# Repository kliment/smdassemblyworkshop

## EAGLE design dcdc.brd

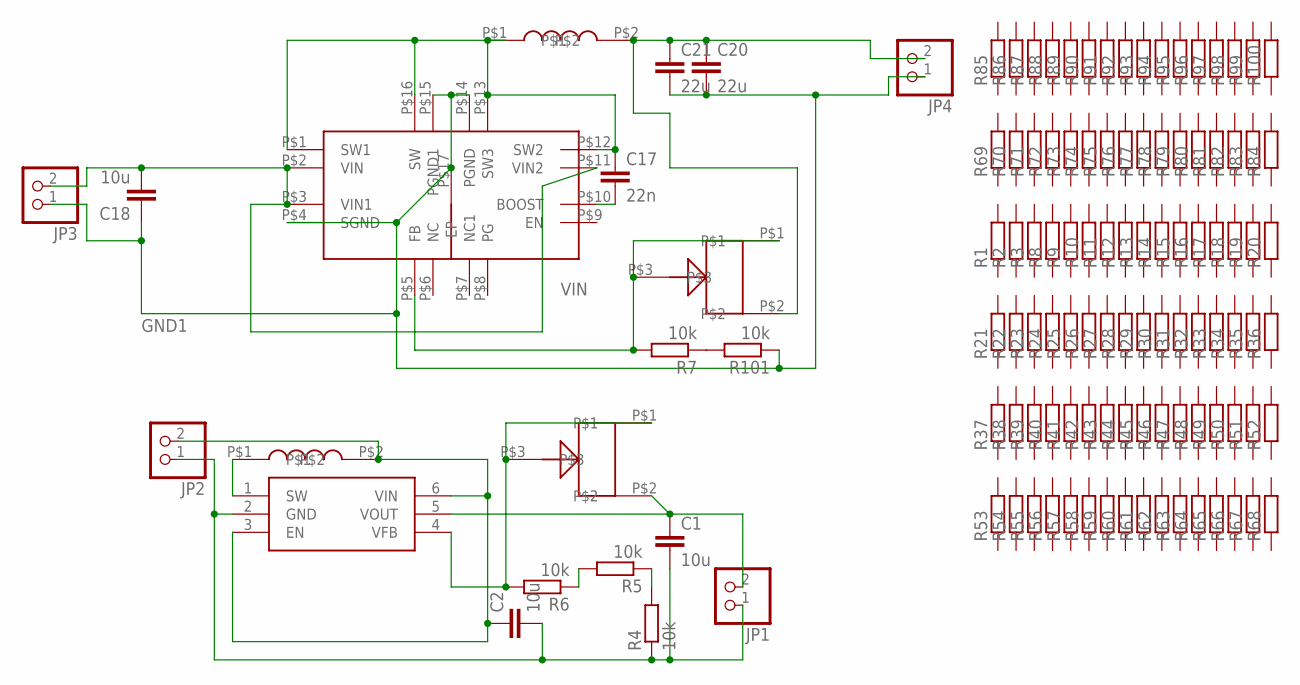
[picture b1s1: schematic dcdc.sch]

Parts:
C1, C2, C18: 10u; C1206K
C17: 22n; C0603
C20, C21: 22u; C1206K
JP1, JP2, JP3, JP4: PINHD-1X2; 1X02
R1, R2, R3, R8, R9, R10, R11, R12, R13, R14, R15, R16, R17, R18, R19, R20, R21, R22, R23, R24, R25, R26, R27, R28, R29, R30, R31, R32, R33, R34, R35, R36, R69, R70, R71, R72, R73, R74, R75, R76, R77, R78, R79, R80, R81, R82, R83, R84, R85, R86, R87, R88, R89, R90, R91, R92, R93, R94, R95, R96, R97, R98, R99, R100: R-EU_R0402; R0402
R4, R5, R6, R7, R101: 10k; R0603
R37, R38, R39, R40, R41, R42, R43, R44, R45, R46, R47, R48, R49, R50, R51, R52, R53, R54, R55, R56, R57, R58, R59, R60, R61, R62, R63, R64, R65, R66, R67, R68: R-EU_R0603; R0603
U$1, U$4: TRIMMER3MM
U$2: MCP1640SOT23-6; SOT23-6L
U$3: EPL2014
U$18: NR6028; NRS6
U$19: MCP16323; QFN16

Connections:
GND: C1.2, C2.2, JP1.1, JP2.1, R4.1, U$2.2 (GND)
GND1: C18.1, C20.2, C21.2, JP3.1, JP4.1, R101.1, U$19.P$4 (SGND), U$19.P$14 (PGND), U$19.P$15 (PGND1), U$19.P$17 (EP)
unnamed: R7.2, U$4.P$1, U$4.P$3, U$19.P$5 (FB)
unnamed: R4.2, R5.1
unnamed: C1.1, JP1.2, U$1.P$2, U$2.5 (VOUT)
unnamed: U$2.1 (SW), U$3.P$1
unnamed: R5.2, R6.1
unnamed: C2.1, JP2.2, U$2.3 (EN), U$2.6 (VIN), U$3.P$2
unnamed: R7.1, R101.2
unnamed: R6.2, U$1.P$1, U$1.P$3, U$2.4 (VFB)
unnamed: C17.2, U$19.P$10 (BOOST)
SW: C17.1, U$18.P$1, U$19.P$1 (SW1), U$19.P$12 (SW2), U$19.P$13 (SW3), U$19.P$16 (SW)
VIN: C18.2, JP3.2, U$19.P$2 (VIN), U$19.P$3 (VIN1), U$19.P$11 (VIN2)
VOUT: C20.1, C21.1, JP4.2, U$4.P$2, U$18.P$2

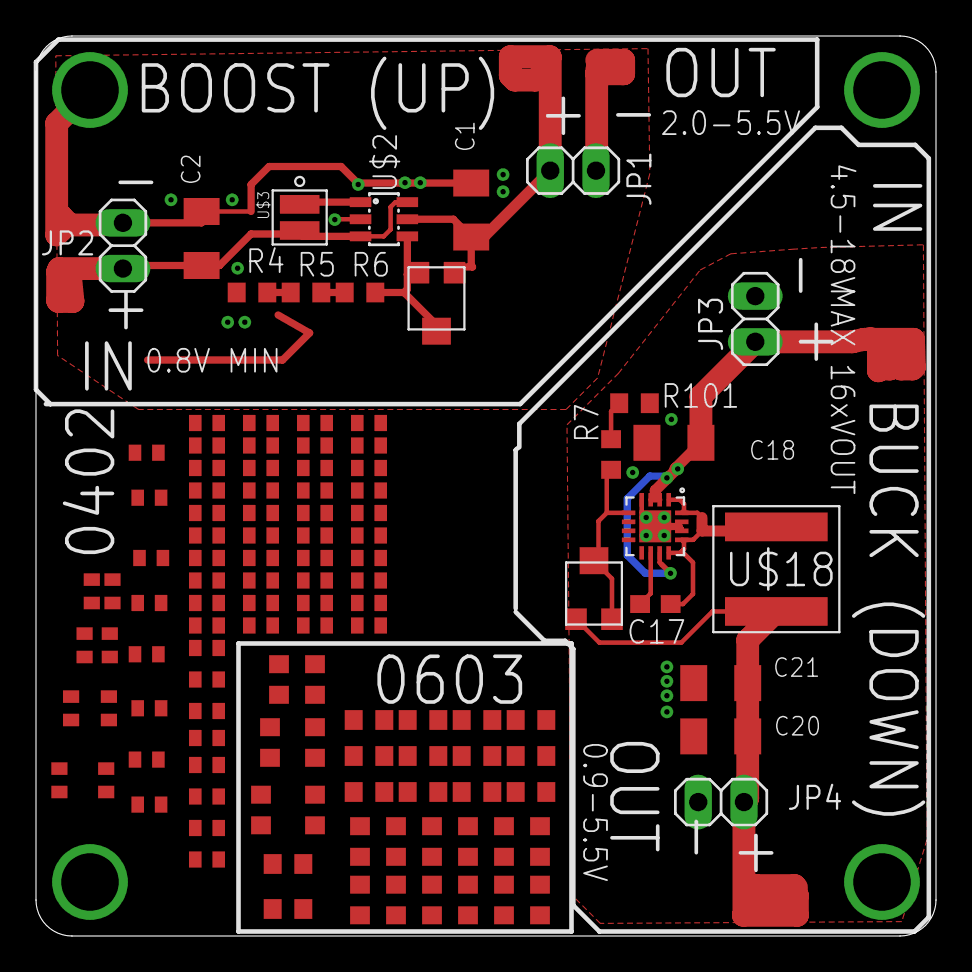
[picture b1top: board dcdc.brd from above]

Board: 2 copper layers, 50.0 x 50.0 mm, 117 parts (0 on the bottom side), 14 nets.

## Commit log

2015-12-27 Add assembly diagram
